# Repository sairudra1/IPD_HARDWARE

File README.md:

the above repository have all the required hardware code 

https://github.com/theprashantsherkar/IPD-2024-25 has the website on which it has to be linked via firebase
its an on-going project

currently you can see the sensor parameter viavalization on webserver hosted by esp32
also in a video you can see the dummy sensor value transfered to the firebase

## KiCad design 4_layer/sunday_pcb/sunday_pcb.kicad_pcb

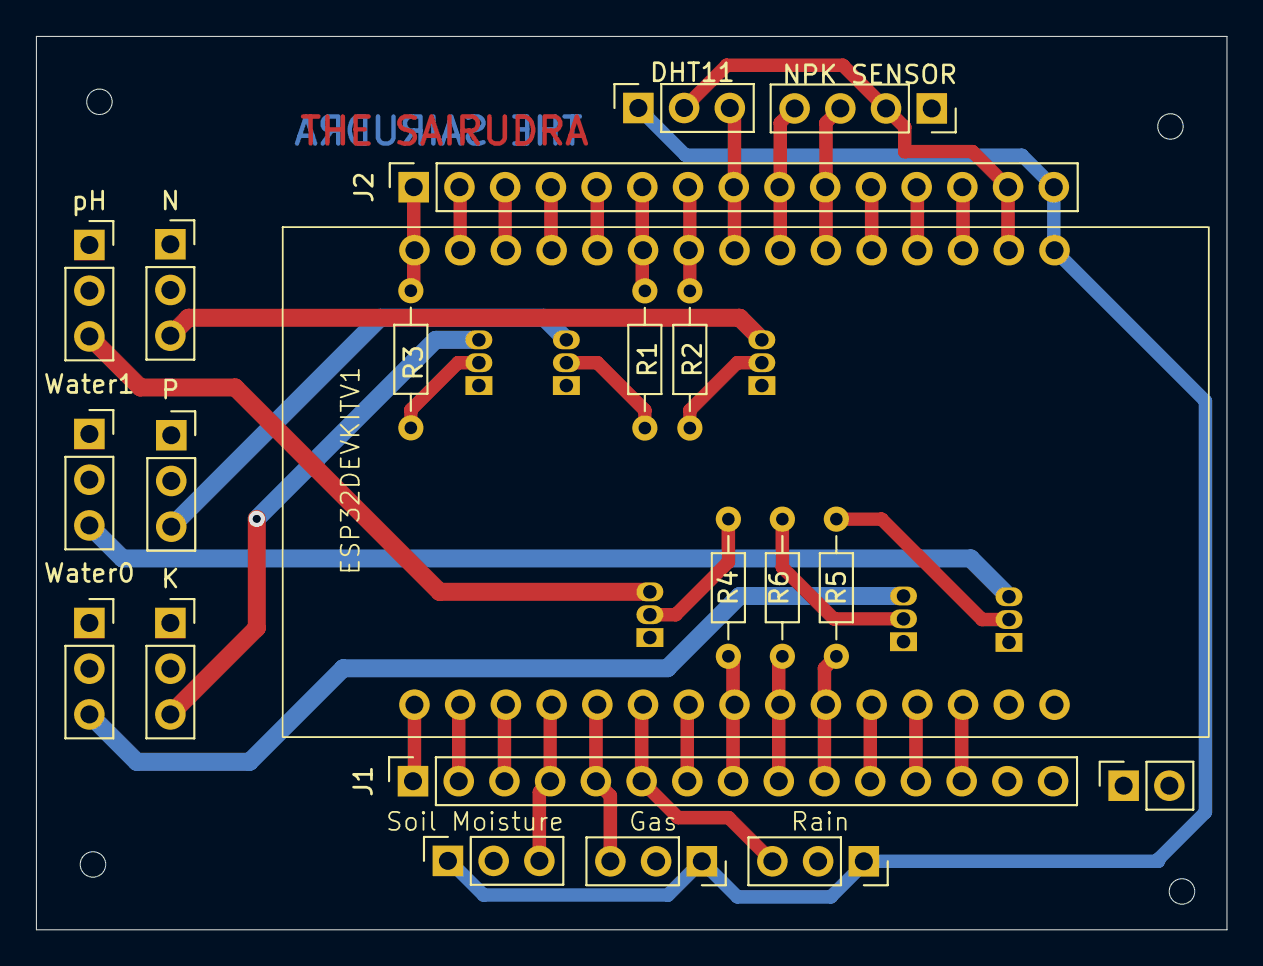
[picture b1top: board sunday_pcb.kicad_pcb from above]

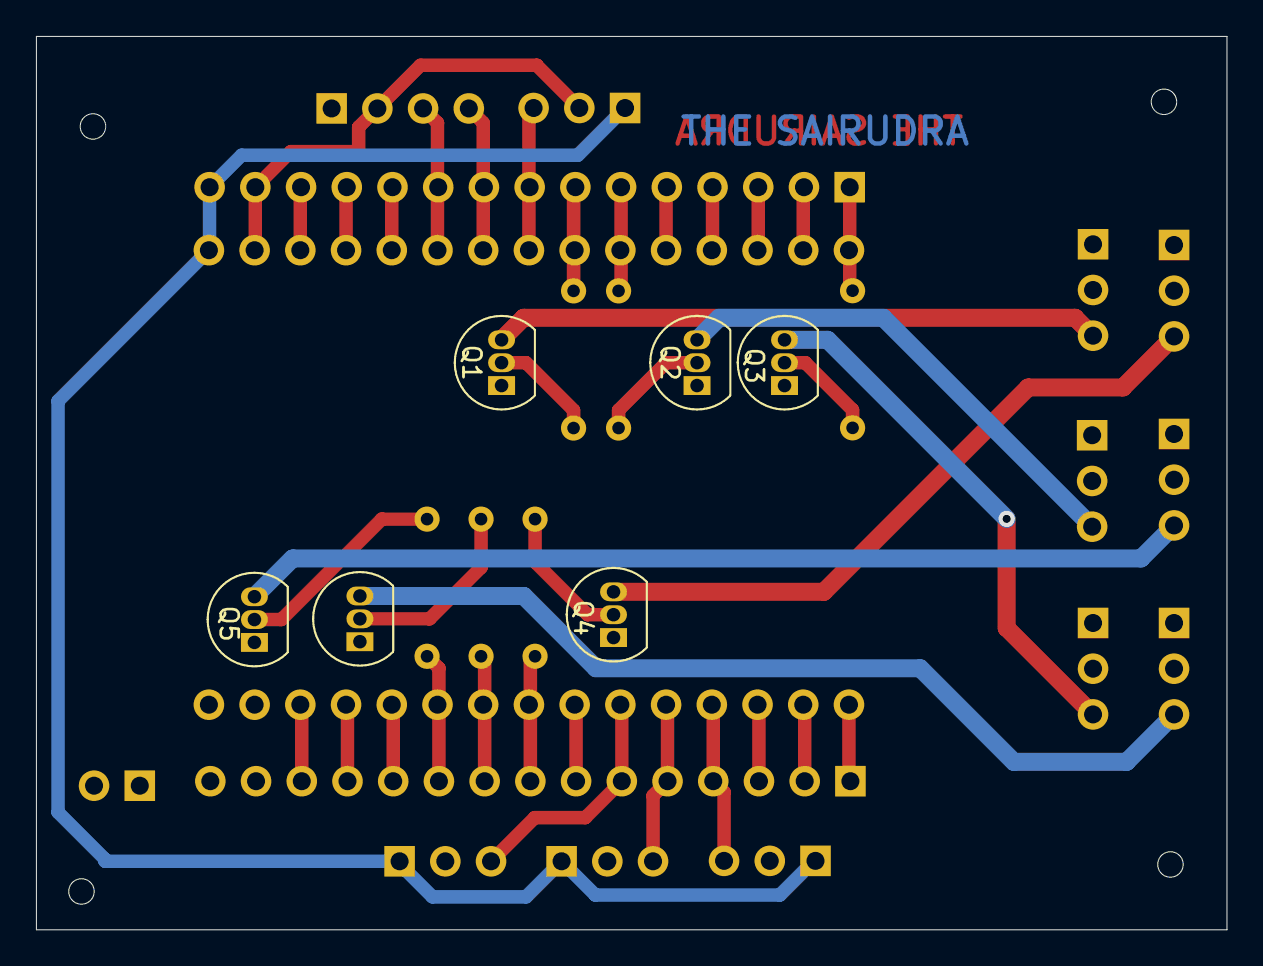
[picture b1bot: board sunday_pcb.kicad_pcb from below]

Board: 4 copper layers, 66.1 x 49.6 mm, 27 parts (6 on the bottom side), 42 nets.

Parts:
DHT11: Conn_01x03_Pin; PinSocket_1x03_P2.54mm_Vertical
ESP32DEVKITV1: ESP32DEVIKITV1
GAS0: Conn_01x03_Pin; PinSocket_1x03_P2.54mm_Vertical
J1, J2: Conn_01x15_Pin; PinSocket_1x15_P2.54mm_Vertical
J3: Conn_01x04_Pin; PinSocket_1x04_P2.54mm_Vertical
K: Conn_01x03_Pin; PinSocket_1x03_P2.54mm_Vertical
N: Conn_01x03_Pin; PinSocket_1x03_P2.54mm_Vertical
P: Conn_01x03_Pin; PinSocket_1x03_P2.54mm_Vertical
PowerIN_1: Battery; PinSocket_1x02_P2.54mm_Vertical
Q1, Q2, Q3, Q4, Q5, Q6: BC547; TO-92_Inline
R1, R2, R3, R4, R5, R6: 1K; R_Axial_DIN0204_L3.6mm_D1.6mm_P7.62mm_Horizontal
RAIN0: Conn_01x03_Pin; PinSocket_1x03_P2.54mm_Vertical
SOIL0: Conn_01x03_Pin; PinSocket_1x03_P2.54mm_Vertical
Water0, Water1: Conn_01x03_Pin; PinSocket_1x03_P2.54mm_Vertical
pH: Conn_01x03_Pin; PinSocket_1x03_P2.54mm_Vertical

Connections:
3V: DHT11.1, ESP32DEVKITV1.16 (3V3), GAS0.1, J2.15, RAIN0.1, SOIL0.1
5V: ESP32DEVKITV1.15 (VIN), J1.15, J3.1, K.1, N.1, P.1, PowerIN_1.1 (+), Q1.1 (C), Q2.1 (C), Q3.1 (C), Q4.1 (C), Q5.1 (C), Q6.1 (C), Water0.1, Water1.1, pH.1
DHT: DHT11.3, ESP32DEVKITV1.23 (D5), J2.8
D_2: ESP32DEVKITV1.19 (D2), J2.12
D_4: ESP32DEVKITV1.20 (D4), J2.11
D_12: ESP32DEVKITV1.12 (D12), J1.12
D_13: ESP32DEVKITV1.13 (D13), J1.13
D_14: ESP32DEVKITV1.11 (D14), J1.11
D_15: ESP32DEVKITV1.18 (D15), J2.13
D_21: ESP32DEVKITV1.26 (D21), J2.5
D_22: ESP32DEVKITV1.29 (D22), J2.2
D_33: ESP32DEVKITV1.7 (D33), J1.7
EN_0: ESP32DEVKITV1.1 (EN), J1.1
ESP_RELAY_K: ESP32DEVKITV1.30 (D23), J2.1, R3.1
ESP_RELAY_N: ESP32DEVKITV1.24 (D18), J2.7, R2.1
ESP_RELAY_P: ESP32DEVKITV1.25 (D19), J2.6, R1.1
ESP_RELAY_W0: ESP32DEVKITV1.9 (D26), J1.9, R6.1
ESP_RELAY_W1: ESP32DEVKITV1.10 (D27), J1.10, R5.1
ESP_RELAY_pH: ESP32DEVKITV1.8 (D25), J1.8, R4.1
GAS: ESP32DEVKITV1.5 (D35), GAS0.3, J1.5
GND: ESP32DEVKITV1.14 (GND), GAS0.2, J1.14, K.2, N.2, P.2, PowerIN_1.2 (-), RAIN0.2, SOIL0.2, Water0.2, Water1.2, pH.2
GND2: DHT11.2, ESP32DEVKITV1.17 (GND), J2.14, J3.2
unnamed: K.3, Q3.3 (E)
unnamed: N.3, Q1.3 (E)
unnamed: P.3, Q2.3 (E)
unnamed: Q1.2 (B), R2.2
unnamed: Q2.2 (B), R1.2
unnamed: Q3.2 (B), R3.2
unnamed: Q4.2 (B), R4.2
unnamed: Q4.3 (E), pH.3
unnamed: Q5.2 (B), R5.2
unnamed: Q5.3 (E), Water1.3
unnamed: Q6.2 (B), R6.2
unnamed: Q6.3 (E), Water0.3
RAIN: ESP32DEVKITV1.6 (D32), J1.6, RAIN0.3
RX2: ESP32DEVKITV1.21 (RX2), J2.10, J3.3
RX_0: ESP32DEVKITV1.27 (RX0), J2.4
SOIL: ESP32DEVKITV1.4 (D34), J1.4, SOIL0.3
TX2: ESP32DEVKITV1.22 (TX2), J2.9, J3.4
TX_0: ESP32DEVKITV1.28 (TX0), J2.3
VN_0: ESP32DEVKITV1.3 (VN), J1.3
VP_0: ESP32DEVKITV1.2 (VP), J1.2

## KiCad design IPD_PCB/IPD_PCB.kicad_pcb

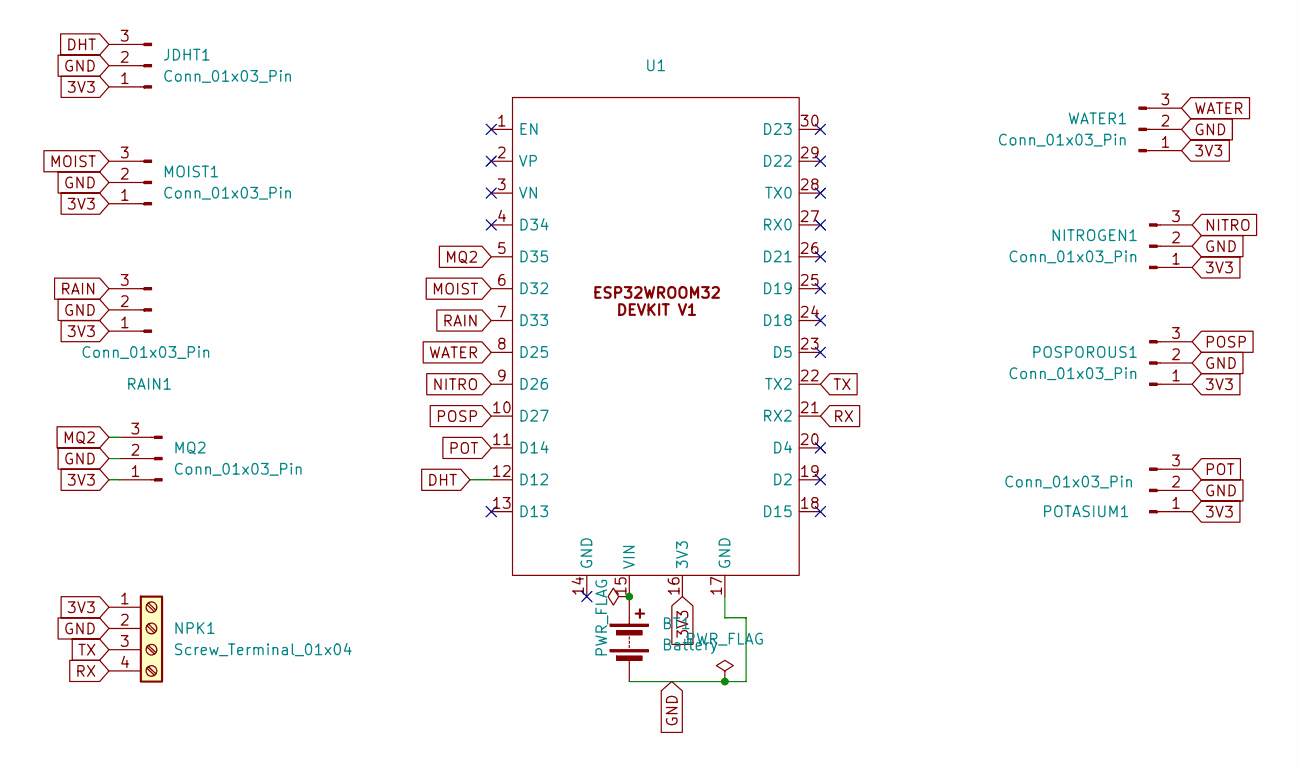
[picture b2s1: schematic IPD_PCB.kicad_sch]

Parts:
BT1: Battery; TerminalBlock_MetzConnect_Type059_RT06302HBWC_1x02_P3.50mm_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
JDHT1: Conn_01x03_Pin; PinHeader_1x03_P2.54mm_Vertical
MOIST1: Conn_01x03_Pin; PinHeader_1x03_P2.54mm_Vertical
MQ2: Conn_01x03_Pin; PinHeader_1x03_P2.54mm_Vertical
NITROGEN1: Conn_01x03_Pin; PinHeader_1x03_P2.54mm_Vertical
NPK1: Screw_Terminal_01x04; TerminalBlock_4Ucon_1x04_P3.50mm_Horizontal
POSPOROUS1: Conn_01x03_Pin; PinHeader_1x03_P2.54mm_Vertical
POTASIUM1: Conn_01x03_Pin; PinHeader_1x03_P2.54mm_Vertical
RAIN1: Conn_01x03_Pin; PinHeader_1x03_P2.54mm_Vertical
U1: ESP32DEVIKITV1
WATER1: Conn_01x03_Pin; PinHeader_1x03_P2.54mm_Vertical

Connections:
3V3: JDHT1.1, MOIST1.1, MQ2.1, NITROGEN1.1, NPK1.1, POSPOROUS1.1, POTASIUM1.1, RAIN1.1, U1.16 (3V3), WATER1.1; also elsewhere on the board
DHT: JDHT1.3, U1.12 (D12); also elsewhere on the board
GND: BT1.2 (-), JDHT1.2, MOIST1.2, MQ2.2, NITROGEN1.2, NPK1.2, POSPOROUS1.2, POTASIUM1.2, RAIN1.2, U1.17 (GND), WATER1.2; also elsewhere on the board
MOIST: MOIST1.3, U1.6 (D32); also elsewhere on the board
MQ2: MQ2.3, U1.5 (D35); also elsewhere on the board
NITRO: NITROGEN1.3, U1.9 (D26); also elsewhere on the board
unnamed 6: BT1.1 (+), U1.15 (VIN); also elsewhere on the board
POSP: POSPOROUS1.3, U1.10 (D27); also elsewhere on the board
POT: POTASIUM1.3, U1.11 (D14); also elsewhere on the board
RAIN: RAIN1.3, U1.7 (D33); also elsewhere on the board
RX: NPK1.4, U1.21 (RX2); also elsewhere on the board
TX: NPK1.3, U1.22 (TX2); also elsewhere on the board
WATER: U1.8 (D25), WATER1.3; also elsewhere on the board

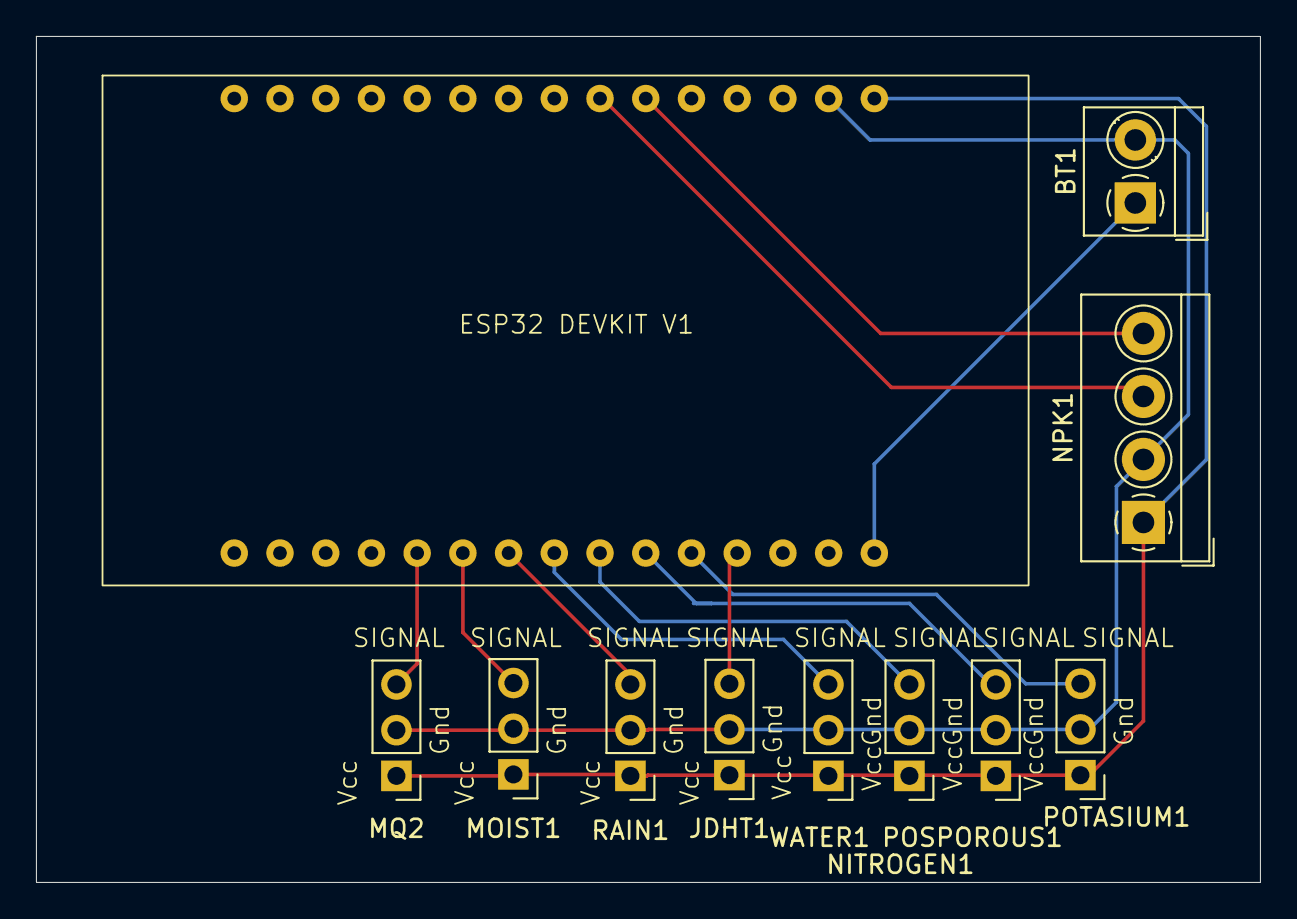
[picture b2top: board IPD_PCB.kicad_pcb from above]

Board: 2 copper layers, 68.0 x 47.0 mm, 11 parts (0 on the bottom side), 13 nets.

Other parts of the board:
ESP32 DEVKIT V1: ESP32DEVIKITV1

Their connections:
3V3: ESP32 DEVKIT V1.16 (3V3); also elsewhere on the board
DHT: ESP32 DEVKIT V1.12 (D12); also elsewhere on the board
GND: ESP32 DEVKIT V1.17 (GND); also elsewhere on the board
MOIST: ESP32 DEVKIT V1.6 (D32); also elsewhere on the board
MQ2: ESP32 DEVKIT V1.5 (D35); also elsewhere on the board
NITRO: ESP32 DEVKIT V1.9 (D26); also elsewhere on the board
unnamed 6: ESP32 DEVKIT V1.15 (VIN); also elsewhere on the board
POSP: ESP32 DEVKIT V1.10 (D27); also elsewhere on the board
POT: ESP32 DEVKIT V1.11 (D14); also elsewhere on the board
RAIN: ESP32 DEVKIT V1.7 (D33); also elsewhere on the board
RX: ESP32 DEVKIT V1.21 (RX2); also elsewhere on the board
TX: ESP32 DEVKIT V1.22 (TX2); also elsewhere on the board
WATER: ESP32 DEVKIT V1.8 (D25); also elsewhere on the board

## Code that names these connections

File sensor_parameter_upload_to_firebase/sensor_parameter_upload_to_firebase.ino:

#include <WiFi.h>
#include <Firebase_ESP_Client.h>

#define WIFI_SSID "Sairudra"
#define WIFI_PASSWORD "12345678"
#include <DHT.h>
int soilMoisture = 0;
int gasValue = 0;
int hum, temp;
bool rainD = false;
const char* ssid = "Sairudra";
const char* password = "12345678";
float temperature = 0;
float humidity = 0;
bool rainDetected = false;
int smoisture = 0;
bool smoke = false;
// Pin configurations
#define DHTPIN 5            // DHT11 data pin
#define DHTTYPE DHT11       // DHT11 sensor type
#define SOIL_SENSOR_PIN 34  // Soil moisture sensor pin (analog)
#define GAS_SENSOR_PIN 35   // MQ2 gas sensor pin (analog)
#define RAIN_SENSOR_PIN 32  // Rain sensor pin (digital)
#define PUMP_PIN 23         // Water pump control pin (relay)

// Sensor objects and variables
DHT dht(DHTPIN, DHTTYPE);
bool pumpState = false;  // Default pump state (OFF)

/* 2. Define the API Key */
#define API_KEY "AIzaSyCAmlESSeubeorQfZrhlo_n2AAyLU6EVj4"

/* 3. Define the RTDB URL */
#define DATABASE_URL "https://newyearesp-default-rtdb.firebaseio.com/"

/* 4. Define the user Email and password that alreadey registerd or added in your project */
#define USER_EMAIL "sairudragudur@gmail.com"
#define USER_PASSWORD "Sairudra@123"

// Define Firebase Data object
FirebaseData fbdo;

FirebaseAuth auth;
FirebaseConfig config;

unsigned long sendDataPrevMillis = 0;

const int ledPin = 4;

void setup() {

  Serial.begin(115200);
  WiFi.begin(WIFI_SSID, WIFI_PASSWORD);

  dht.begin();

  // GPIO setup
  pinMode(PUMP_PIN, OUTPUT);
  pinMode(RAIN_SENSOR_PIN, INPUT);
  digitalWrite(PUMP_PIN, LOW);
  Serial.print("Connecting to Wi-Fi");
  while (WiFi.status() != WL_CONNECTED) {
    Serial.print(".");
    delay(300);
  }
  Serial.println();
  Serial.print("Connected with IP: ");
  Serial.println(WiFi.localIP());
  Serial.println();

  /* Assign the api key (required) */
  config.api_key = API_KEY;

  /* Assign the user sign in credentials */
  auth.user.email = USER_EMAIL;
  auth.user.password = USER_PASSWORD;

  /* Assign the RTDB URL (required) */
  config.database_url = DATABASE_URL;

  // Comment or pass false value when WiFi reconnection will control by your code or third party library e.g. WiFiManager
  Firebase.reconnectNetwork(true);

  // Since v4.4.x, BearSSL engine was used, the SSL buffer need to be set.
  // Large data transmission may require larger RX buffer, otherwise connection issue or data read time out can be occurred.
  fbdo.setBSSLBufferSize(4096, 1024);

  // Limit the size of response payload to be collected in FirebaseData
  fbdo.setResponseSize(2048);

  Firebase.begin(&config, &auth);

  Firebase.setDoubleDigits(5);

  config.timeout.serverResponse = 10 * 1000;
}

void sensor() {
  humidity = dht.readHumidity();               //humidity
  temperature = dht.readTemperature();         //temperature
  soilMoisture = analogRead(SOIL_SENSOR_PIN);  //
  gasValue = analogRead(GAS_SENSOR_PIN);
  rainDetected = digitalRead(RAIN_SENSOR_PIN);
  if (gasValue >=  2048) {
    smoke = true;
  } else{
    smoke = false;
  }
  smoisture = map(soilMoisture, 0, 4095, 100, 0);
  if (rainDetected) {
    rainD = false;
  } else {
    rainD = true;  //bollen rail detected or not
  }
}
void loop() {

  // Firebase.ready() should be called repeatedly to handle authentication tasks.
  if (Firebase.ready() && (millis() - sendDataPrevMillis > 1000 || sendDataPrevMillis == 0)) {
    sendDataPrevMillis = millis();

    sensor();
    if (Firebase.RTDB.setFloat(&fbdo, "sensor/temperature", temperature)) {
      Serial.print("temperature level : ");
      Serial.println(temperature);
    } else {
      Serial.println("FAILED");
      Serial.println("REASON: " + fbdo.errorReason());
    }
    if (Firebase.RTDB.setFloat(&fbdo, "sensor/humidity", humidity)) {
      Serial.print("humidity level : ");
      Serial.println(humidity);
    } else {
      Serial.println("FAILED");
      Serial.println("REASON: " + fbdo.errorReason());
    }
    if (Firebase.RTDB.setInt(&fbdo, "sensor/soil_mositure", smoisture)) {
      Serial.print("soil moisture level : ");
      Serial.println(smoisture);
    } else {
      Serial.println("FAILED");
      Serial.println("REASON: " + fbdo.errorReason());
    }
    if (Firebase.RTDB.setBool(&fbdo, "sensor/smoke", smoke)) {
      Serial.print("soil moisture level : ");
      Serial.println(smoke);
    } else {
      Serial.println("FAILED");
      Serial.println("REASON: " + fbdo.errorReason());
    }
    if (Firebase.RTDB.setBool(&fbdo, "sensor/Rain", rainD)) {
      Serial.print("rain? : ");
      Serial.println(rainD);
    } else {
      Serial.println("FAILED");
      Serial.println("REASON: " + fbdo.errorReason());
    }






    /*
    if (Firebase.RTDB.getBool(&fbdo, "/LED/digital")) {
      if (fbdo.dataType() == "boolean") {
        ledStatus = fbdo.boolData();
        Serial.print("LED Status: ");
        Serial.println(ledStatus);
        digitalWrite(LED2_PIN, ledStatus);
      }
    } else {
      Serial.println("FAILED to read LED Status: " + fbdo.errorReason());
    }
    if (Firebase.RTDB.setInt(&fbdo, "test/int", sensorValue)) {
      Serial.print("pot level : ");
      Serial.println(sensorValue);
    } else {
      Serial.println("FAILED");
      Serial.println("REASON: " + fbdo.errorReason());
    }
    if (Firebase.RTDB.setFloat(&fbdo, "Sensor/voltage", voltage)) {
      Serial.print("Voltage: ");
      Serial.println(voltage);
    } else {
      Serial.println("FAILED to save Voltage: " + fbdo.errorReason());
    }
    if (Firebase.RTDB.getInt(&fbdo, "/led/state", &ledState)) {
      digitalWrite(ledPin, ledState);
    } else {
      Serial.println(fbdo.errorReason().c_str());
    }
    */
  }
}

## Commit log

2025-04-12 final update
2025-04-12 localhost code
2025-07-06 ESP32 CAM library
